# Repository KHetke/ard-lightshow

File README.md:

# ard-lightshow
Arduino Christmas light show implemented using WiFi modules and FFT

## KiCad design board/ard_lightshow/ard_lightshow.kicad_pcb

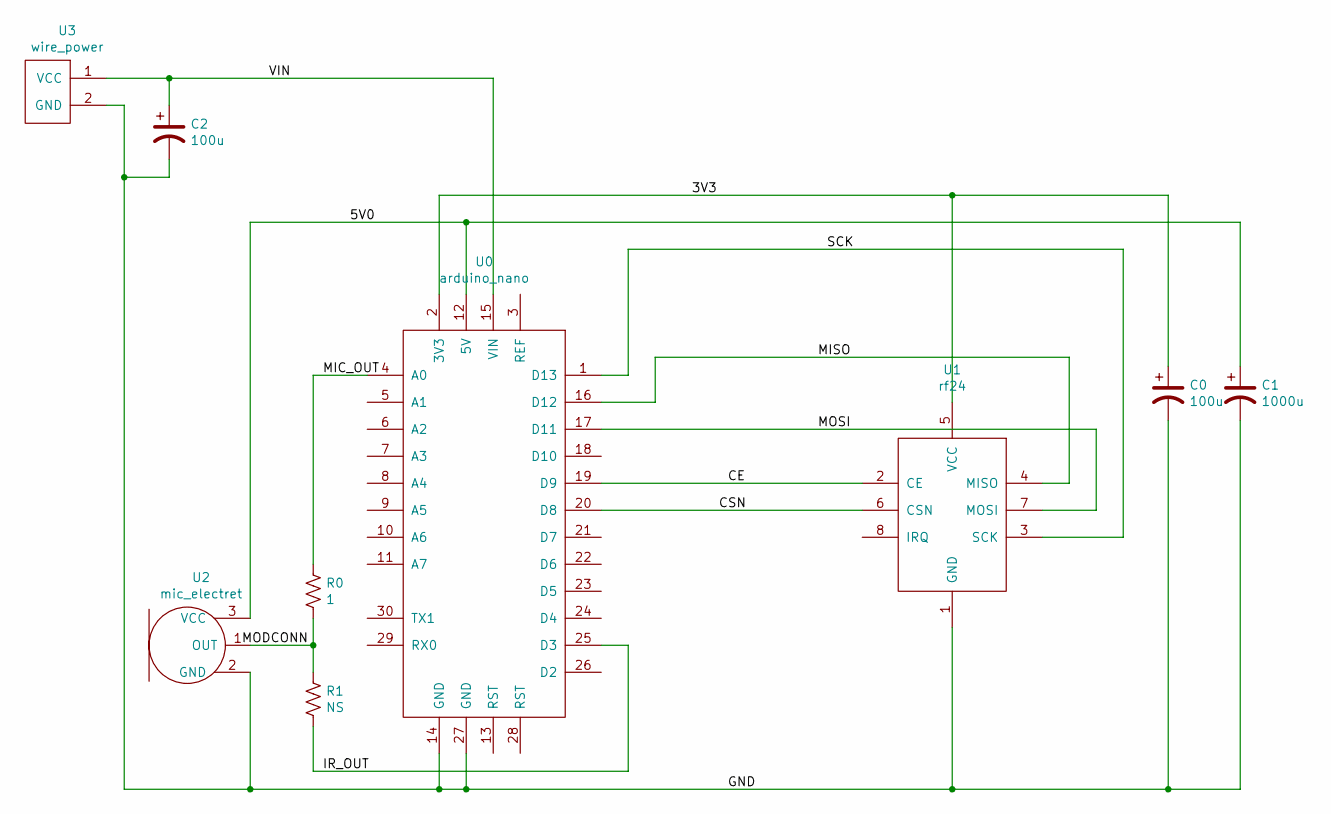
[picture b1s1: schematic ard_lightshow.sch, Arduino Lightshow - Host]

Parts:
C0, C2: 100u; CP_Radial_D5.0mm_P2.50mm
C1: 1000u; CP_Radial_D8.0mm_P3.50mm
R0: 1; R_0805
R1: NS; R_0805
U0: arduino_nano
U1: rf24
U2: mic_electret
U3: wire_power

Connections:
/3V3: C0.1, U0.2 (3V3), U1.5 (VCC)
/5V0: C1.1, U0.12 (5V), U2.3 (VCC)
/CE: U0.19 (D9), U1.2 (CE)
/CSN: U0.20 (D8), U1.6 (CSN)
/GND: C0.2, C1.2, C2.2, U0.14 (GND), U0.27 (GND), U1.1 (GND), U2.2 (GND), U3.2 (GND)
/IR_OUT: R1.2, U0.25 (D3)
/MIC_OUT: R0.1, U0.4 (A0)
/MISO: U0.16 (D12), U1.4 (MISO)
/MOSI: U0.17 (D11), U1.7 (MOSI)
/SCK: U0.1 (D13), U1.3 (SCK)
/VIN: C2.1, U0.15 (VIN), U3.1 (VCC)
unnamed: R0.2, R1.1, U2.1 (OUT)

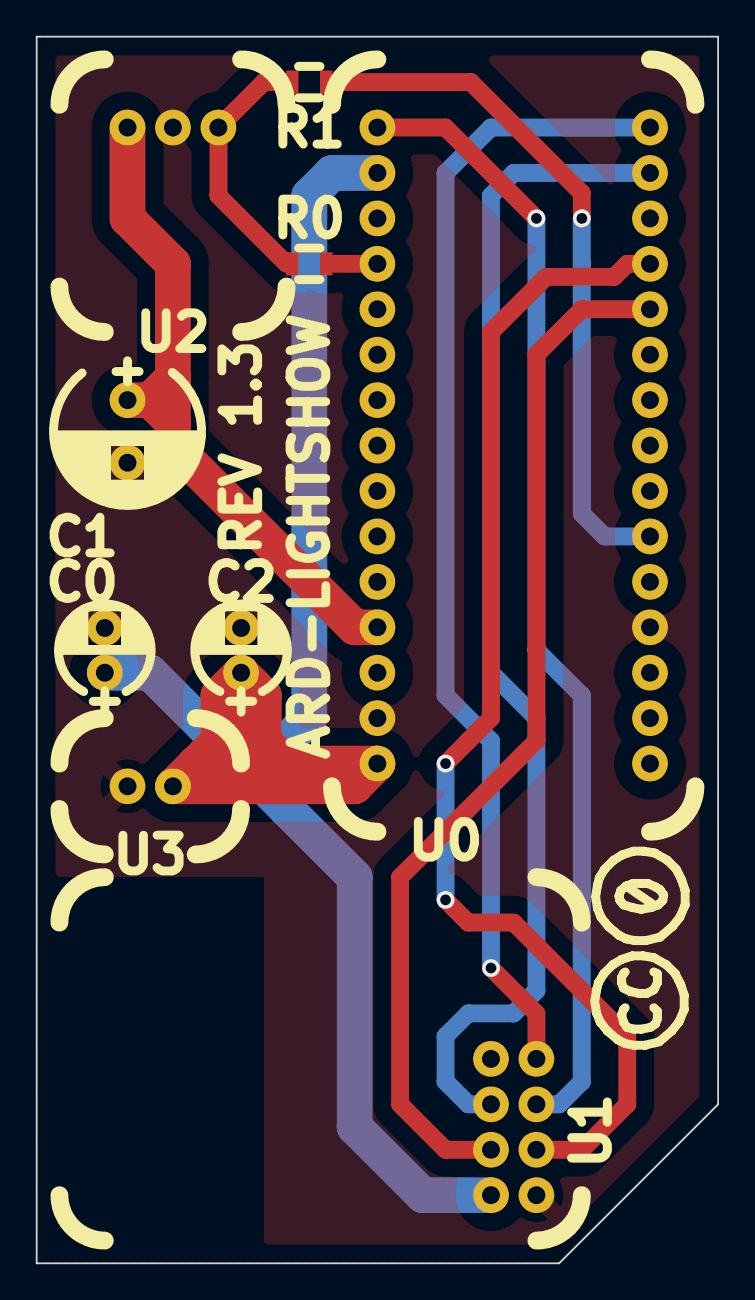
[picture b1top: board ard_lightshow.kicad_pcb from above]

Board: 2 copper layers, 38.1 x 68.6 mm, 10 parts (0 on the bottom side), 12 nets.

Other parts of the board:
 : Symbol_CreativeCommonsPublicDomain_SilkScreenTop_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; Symbol_CreativeCommonsPublicDomain_SilkScreenTop_Small

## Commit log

2020-11-14 Takes an FFT of microphone input and converts to toggle bits.
2020-11-15 Swapped to a host-client architecture
2020-11-15 Radio now transmits from host to client
2020-11-16 Corrected for loop to allow all addresses to be used.
2020-11-16 Updated with correct IR code configuration (Non-standard NEC).
2020-11-17 Receiver now properly takes RF Commands and sends an IR command. Tranceiver now sends a visualization stream to address "AL000".
2020-11-18 Reduced delays in host and client main loops
2020-11-18 Created -Host and -Client PCBs and schematics in KiCad.
2020-11-18 Create LICENSE
2020-11-18 Swapped to a single PCB with 0402 SMD resistors that can be solder jumped for either configuration.
2020-11-18 Added Gerber files for CAM.
2020-11-20 Uniformized via sizes and increased to 2mm copper for easier manufacture.
2020-11-22 Bumped up isolation and decals/solder mask to aid in micro-batch CNC milling.
2020-11-24 Updated PCB vias to 1.0mm/0.6mm drill holes for ease of via rivetting.
